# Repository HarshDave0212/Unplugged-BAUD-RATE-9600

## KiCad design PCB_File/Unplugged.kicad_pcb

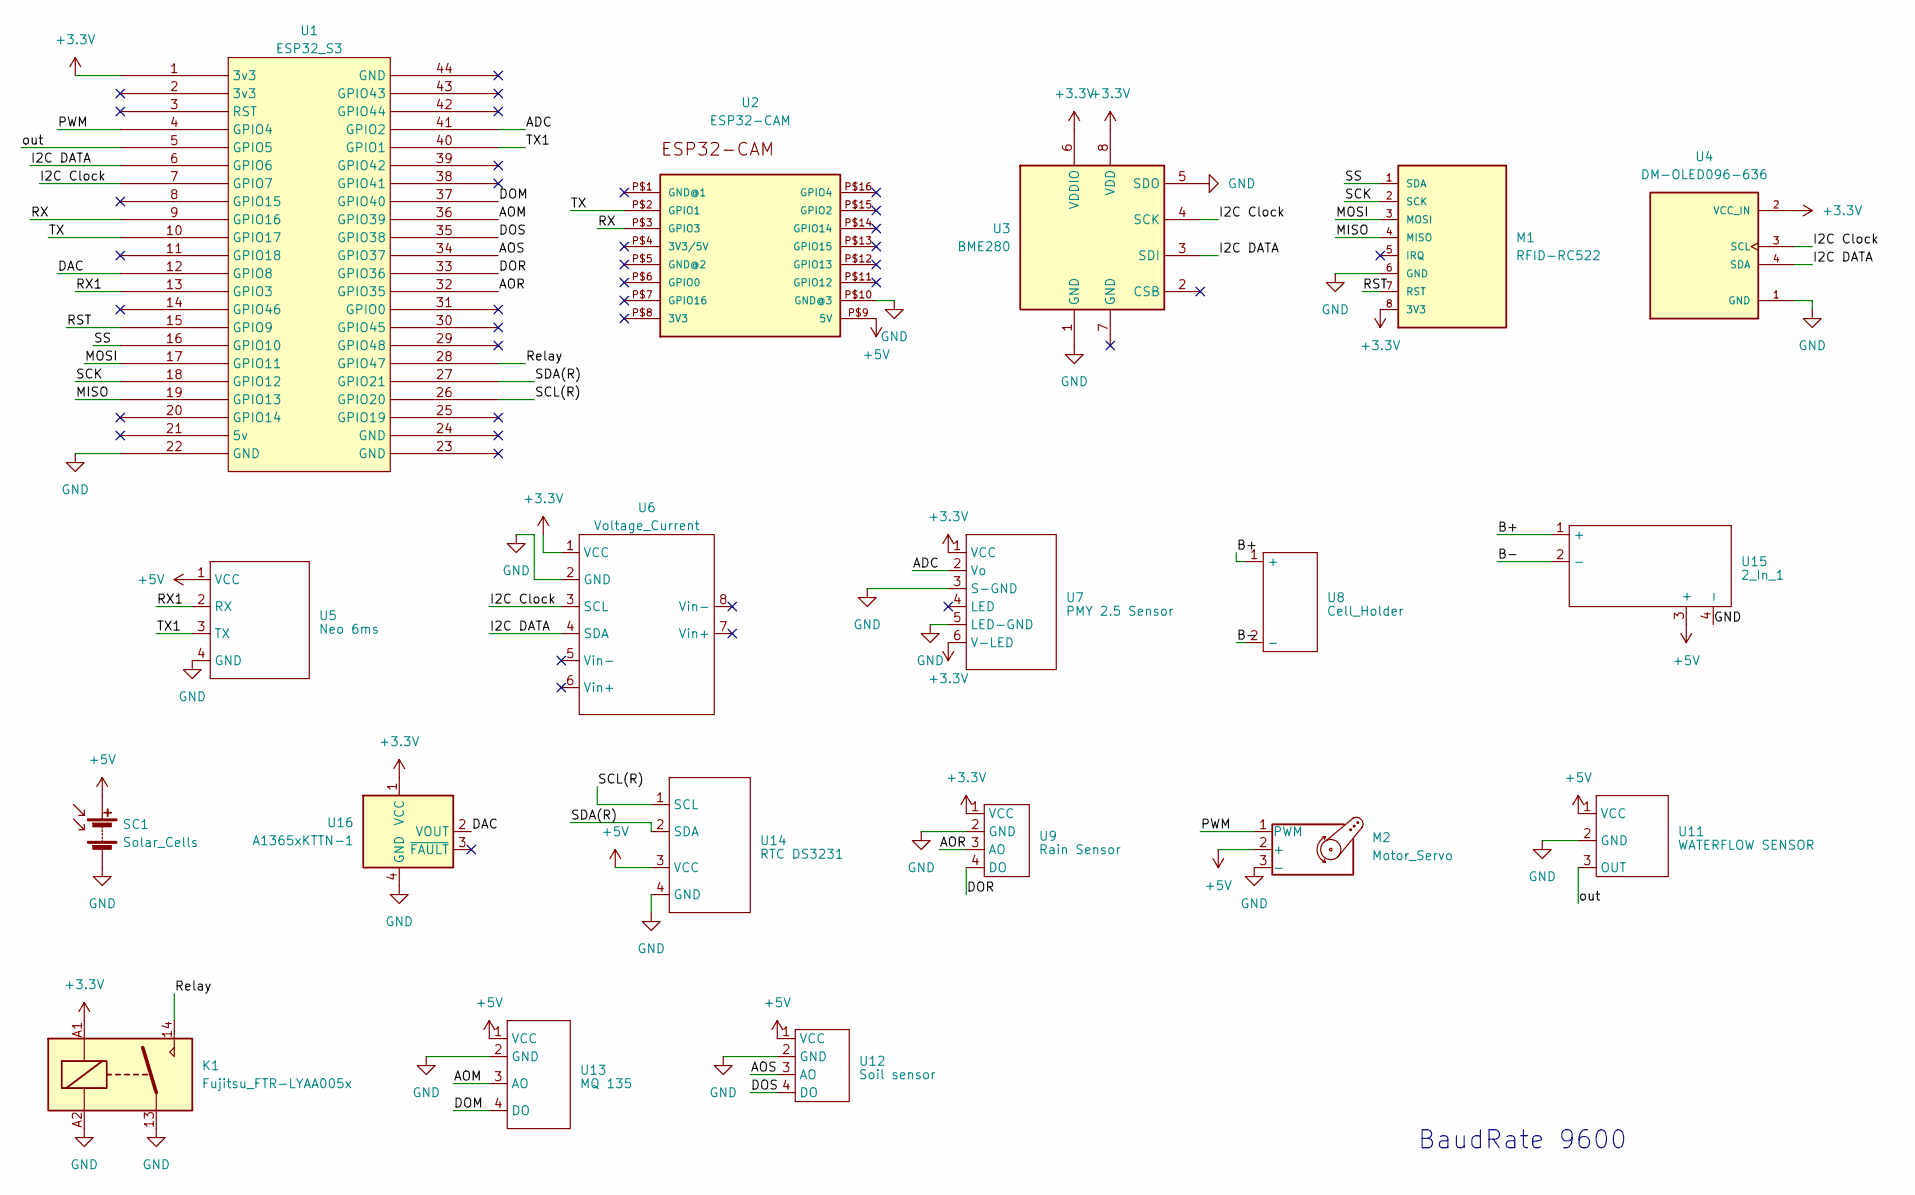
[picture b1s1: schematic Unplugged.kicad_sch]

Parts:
K1: Fujitsu_FTR-LYAA005x; Relay_SPST-NO_Fujitsu_FTR-LYAA005x_FormA_Vertical
M1: RFID-RC522; mrfc522; MPN RFID-RC522
M2: Motor_Servo; Servo Motor
SC1: Solar_Cells; SOLAR_CELL
U1: ESP32_S3; ESP32S3
U2: ESP32-CAM
U3: BME280; Bosch_LGA-8_2.5x2.5mm_P0.65mm_ClockwisePinNumbering
U4: DM-OLED096-636; MODULE_DM-OLED096-636; PARTREV 2018-09-10
U5: Neo 6ms; NEO6M
U6: Voltage_Current; INA219CV
U7: PMY 2.5 Sensor; PinHeader_1x06_P1.00mm_Vertical
U8: Cell_Holder
U9: Rain Sensor; RTC
U11: WATERFLOW SENSOR; Servo Motor
U12: Soil sensor; Soil
U13: MQ 135
U14: RTC DS3231; RTC
U15: 2_In_1
U16: A1365xKTTN-1; Allegro_SIP-4

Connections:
+3.3V: K1.A1, M1.8 (3V3), U1.1 (3v3), U3.6 (VDDIO), U3.8 (VDD), U4.2 (VCC_IN), U6.1 (VCC), U7.1 (VCC), U7.6 (V-LED), U9.1 (VCC), U16.1 (VCC)
+5V: M2.2 (+), SC1.1 (+), U2.P$9 (5V), U5.1 (VCC), U11.1 (VCC), U12.1 (VCC), U13.1 (VCC), U14.3 (VCC), U15.3 (+)
/ADC: U1.41 (GPIO2), U7.2 (Vo)
/AOM: U1.36 (GPIO39), U13.3 (AO)
/AOR: U1.32 (GPIO35), U9.3 (AO)
/AOS: U1.34 (GPIO37), U12.3 (AO)
/B+: U8.1 (+), U15.1 (+)
/B-: U8.2 (-), U15.2 (-)
/DAC: U1.12 (GPIO8), U16.2 (VOUT)
/DOM: U1.37 (GPIO40), U13.4 (DO)
/DOR: U1.33 (GPIO36), U9.4 (DO)
/DOS: U1.35 (GPIO38), U12.4 (DO)
/I2C Clock: U1.7 (GPIO7), U3.4 (SCK), U4.3 (SCL), U6.3 (SCL)
/I2C DATA: U1.6 (GPIO6), U3.3 (SDI), U4.4 (SDA), U6.4 (SDA)
/MISO: M1.4 (MISO), U1.19 (GPIO13)
/MOSI: M1.3 (MOSI), U1.17 (GPIO11)
/PWM: M2.1 (PWM), U1.4 (GPIO4)
/RST: M1.7 (RST), U1.15 (GPIO9)
/RX: U1.9 (GPIO16), U2.P$3 (GPIO3)
/RX1: U1.13 (GPIO3), U5.2 (RX)
/Relay: K1.14, U1.28 (GPIO47)
/SCK: M1.2 (SCK), U1.18 (GPIO12)
/SCL(R): U1.26 (GPIO20), U14.1 (SCL)
/SDA(R): U1.27 (GPIO21), U14.2 (SDA)
/SS: M1.1 (SDA), U1.16 (GPIO10)
/TX: U1.10 (GPIO17), U2.P$2 (GPIO1)
/TX1: U1.40 (GPIO1), U5.3 (TX)
/out: U1.5 (GPIO5), U11.3 (OUT)
GND: K1.13, K1.A2, M1.6 (GND), M2.3 (-), SC1.2 (-), U1.22 (GND), U2.P$10 (GND@3), U3.1 (GND), U3.5 (SDO), U4.1 (GND), U5.4 (GND), U6.2 (GND), U7.3 (S-GND), U7.5 (LED-GND), U9.2 (GND), U11.2 (GND), U12.2 (GND), U13.2 (GND), U14.4 (GND), U15.4 (-), U16.4 (GND)

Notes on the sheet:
BaudRate 9600

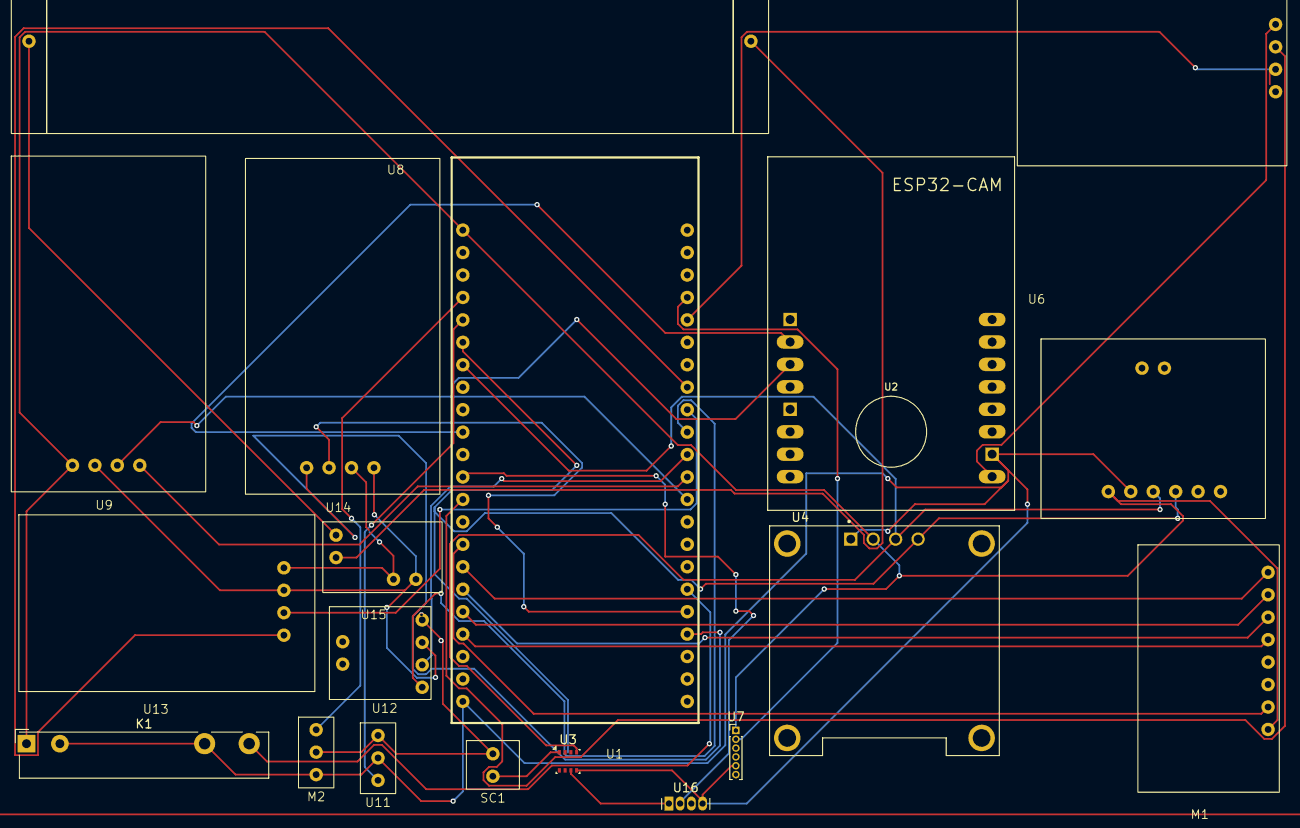
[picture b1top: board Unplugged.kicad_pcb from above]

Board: 2 copper layers, 19 parts (0 on the bottom side), 29 nets.
